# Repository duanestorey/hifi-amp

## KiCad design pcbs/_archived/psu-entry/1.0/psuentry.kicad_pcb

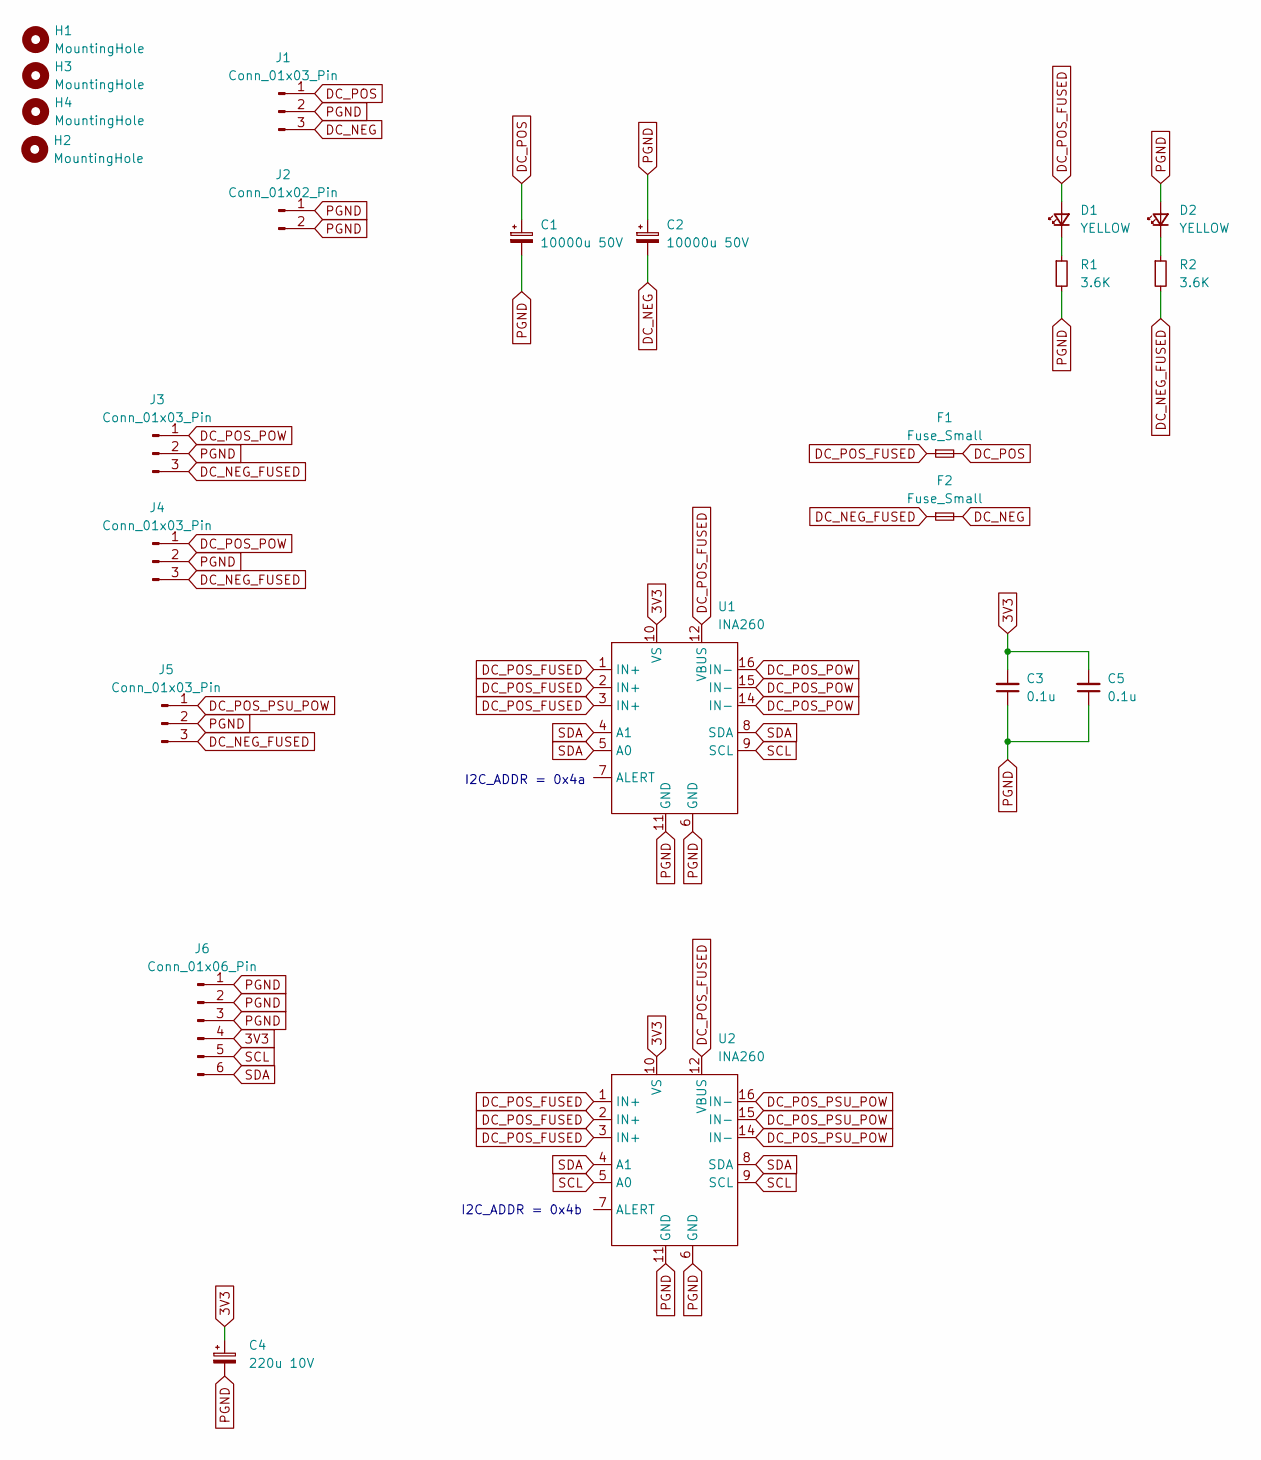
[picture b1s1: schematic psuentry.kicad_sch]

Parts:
C1, C2: 10000u 50V; CP_Radial_D25.0mm_P10.00mm_SnapIn
C3, C5: 0.1u; C_0805_2012Metric_Pad1.18x1.45mm_HandSolder
C4: 220u 10V; CP_Radial_D6.3mm_P2.50mm
D1, D2: YELLOW; LED_0805_2012Metric_Pad1.15x1.40mm_HandSolder
F1, F2: Fuse_Small; Aliexpress Fuse 5x20
H1, H2, H3, H4: MountingHole; MountingHole_3.2mm_M3_DIN965_Pad_TopOnly
J1, J3, J4, J5: Conn_01x03_Pin; JST_VH_B3P-VH-B_1x03_P3.96mm_Vertical
J2: Conn_01x02_Pin; JST_VH_B2P-VH-B_1x02_P3.96mm_Vertical
J6: Conn_01x06_Pin; JST_PH_B6B-PH-K_1x06_P2.00mm_Vertical
R1, R2: 3.6K; R_0603_1608Metric_Pad0.98x0.95mm_HandSolder
U1, U2: INA260; TSSOP-16_4.4x5mm_P0.65mm

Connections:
3V3: C3.2, C4.1, C5.2, J6.4, U1.10 (VS), U2.10 (VS)
DC_NEG: C2.2, F2.2, J1.3
DC_NEG_FUSED: F2.1, J3.3, J4.3, J5.3, R2.2
DC_POS: C1.1, F1.2, J1.1
DC_POS_FUSED: D1.2 (A), F1.1, U1.1 (IN+), U1.2 (IN+), U1.3 (IN+), U1.12 (VBUS), U2.1 (IN+), U2.2 (IN+), U2.3 (IN+), U2.12 (VBUS)
DC_POS_POW: J3.1, J4.1, U1.14 (IN-), U1.15 (IN-), U1.16 (IN-)
DC_POS_PSU_POW: J5.1, U2.14 (IN-), U2.15 (IN-), U2.16 (IN-)
unnamed: D1.1 (K), R1.1
unnamed: D2.1 (K), R2.1
PGND: C1.2, C2.1, C3.1, C4.2, C5.1, D2.2 (A), J1.2, J2.1, J2.2, J3.2, J4.2, J5.2, J6.1, J6.2, J6.3, R1.2, U1.6 (GND), U1.11 (GND), U2.6 (GND), U2.11 (GND)
SCL: J6.5, U1.9 (SCL), U2.5 (A0), U2.9 (SCL)
SDA: J6.6, U1.4 (A1), U1.5 (A0), U1.8 (SDA), U2.4 (A1), U2.8 (SDA)

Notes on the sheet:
I2C_ADDR = 0x4a
I2C_ADDR = 0x4b

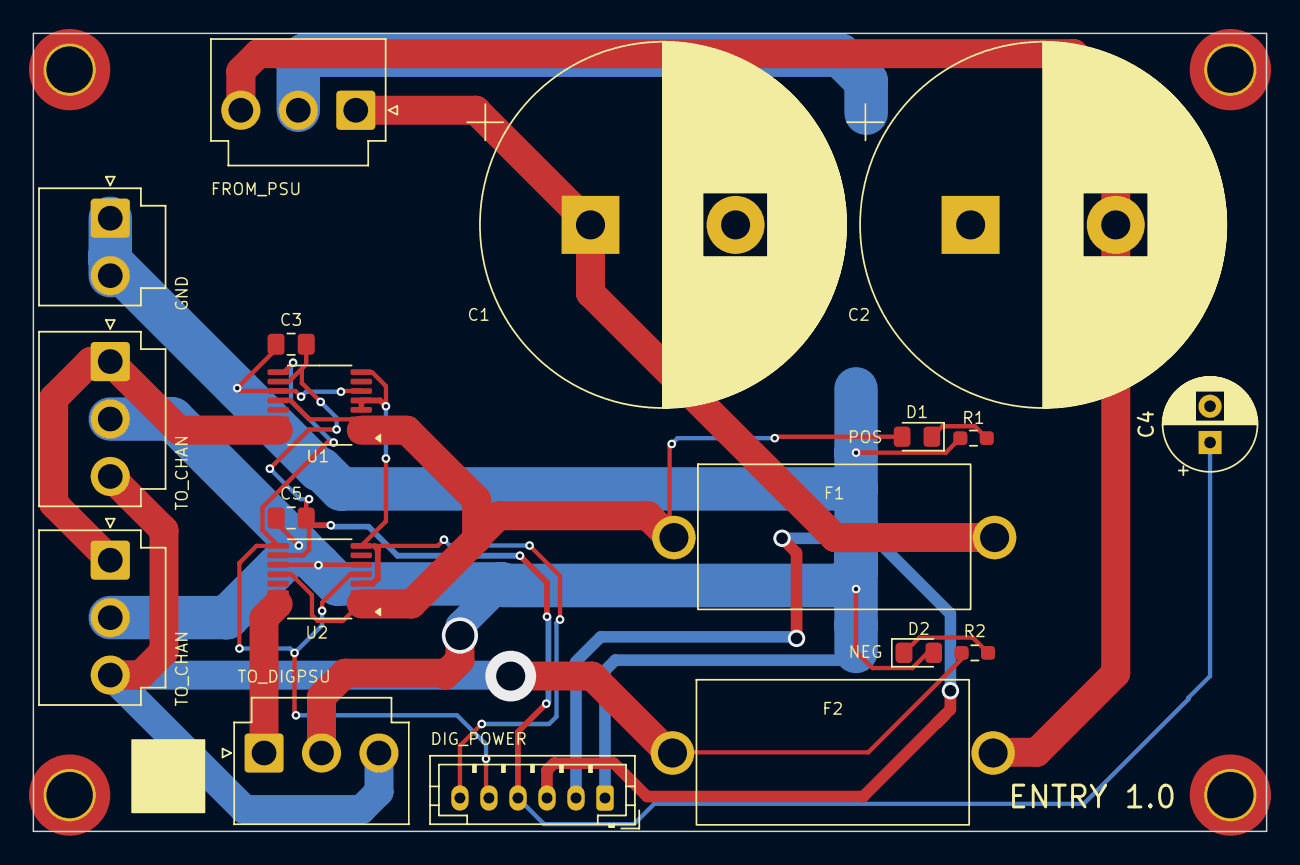
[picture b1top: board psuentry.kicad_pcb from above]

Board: 2 copper layers, 85.0 x 55.0 mm, 23 parts (0 on the bottom side), 12 nets.

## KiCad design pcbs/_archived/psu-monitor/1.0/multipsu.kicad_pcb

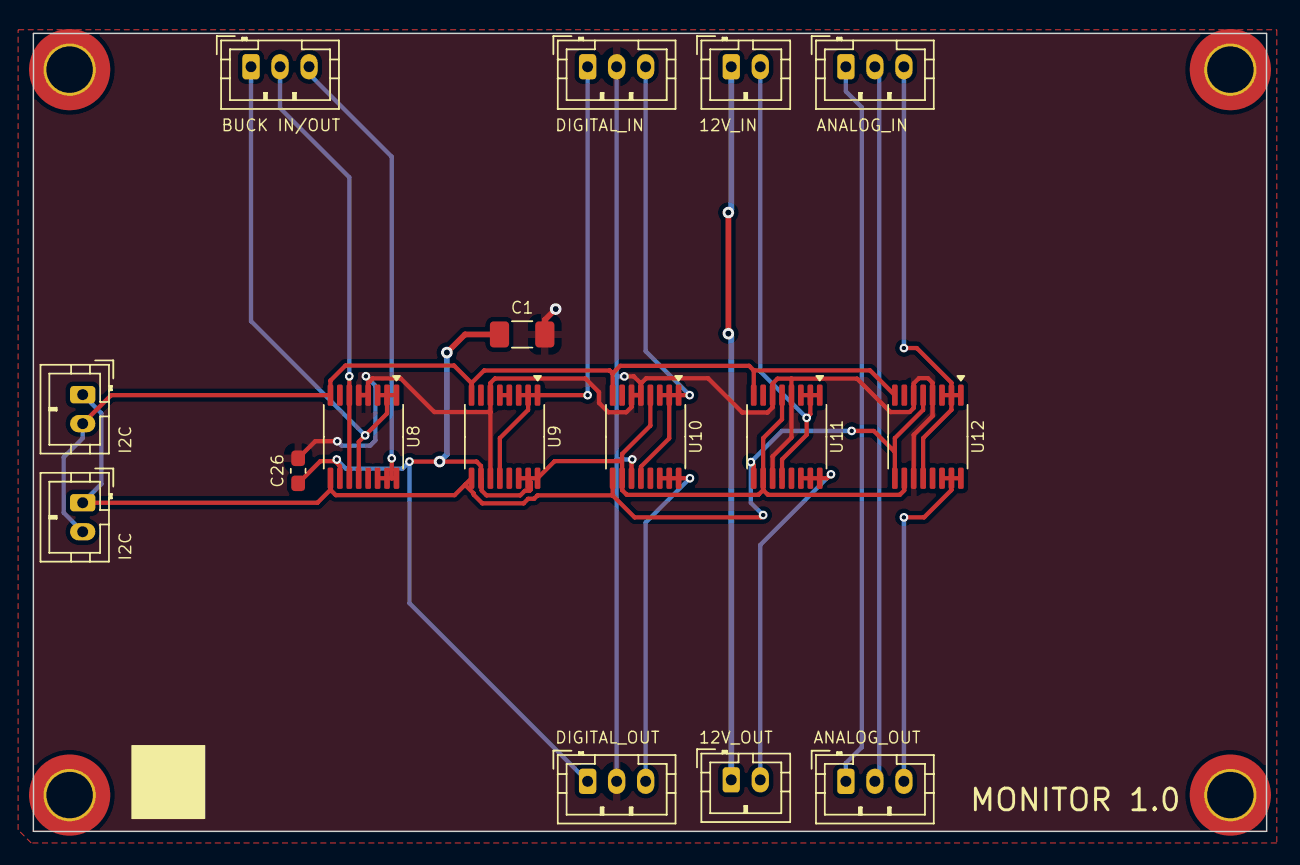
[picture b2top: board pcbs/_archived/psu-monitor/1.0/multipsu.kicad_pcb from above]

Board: 2 copper layers, 85.0 x 55.0 mm, 20 parts (0 on the bottom side), 18 nets.

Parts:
C1: 10u; C_1206_3216Metric_Pad1.33x1.80mm_HandSolder
C26: 0.1U; C_0603_1608Metric_Pad1.08x0.95mm_HandSolder
H1, H2, H3, H4: MountingHole; MountingHole_3.2mm_M3_DIN965_Pad_TopOnly
J1, J2, J5, J6, J7: Conn_01x03_Pin; JST_PH_B3B-PH-K_1x03_P2.00mm_Vertical
J3, J4, J8, J9: Conn_01x02_Pin; JST_PH_B2B-PH-K_1x02_P2.00mm_Vertical
U8, U9, U10, U11, U12: INA260; TSSOP-16_4.4x5mm_P0.65mm

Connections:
3V3: U9.4 (A1), U9.5 (A0)
3V3_IN: J2.1, U9.1 (IN+), U9.2 (IN+), U9.3 (IN+), U9.12 (VBUS)
3V3_OUT: C1.1, C26.1, J5.1, U8.10 (VS), U9.10 (VS), U9.14 (IN-), U9.15 (IN-), U9.16 (IN-), U10.4 (A1), U10.10 (VS), U11.5 (A0), U11.10 (VS), U12.10 (VS)
5V_IN: J2.3, U10.1 (IN+), U10.2 (IN+), U10.3 (IN+), U10.12 (VBUS)
5V_OUT: J5.3, U10.14 (IN-), U10.15 (IN-), U10.16 (IN-)
7V_IN: J1.1, U8.1 (IN+), U8.2 (IN+), U8.3 (IN+), U8.12 (VBUS)
7V_OUT: J1.3, U8.14 (IN-), U8.15 (IN-), U8.16 (IN-)
12V_IN: J8.2, U11.1 (IN+), U11.2 (IN+), U11.3 (IN+), U11.12 (VBUS)
12V_OUT: J4.2, U11.14 (IN-), U11.15 (IN-), U11.16 (IN-)
AGND: J6.2, J7.2
DC_NEG_OUT: J6.1, J7.1
DC_POS_IN: J7.3, U12.1 (IN+), U12.2 (IN+), U12.3 (IN+), U12.12 (VBUS)
DC_POS_OUT: J6.3, U12.14 (IN-), U12.15 (IN-), U12.16 (IN-)
GND: C1.2, C26.2, J2.2, J5.2, U8.4 (A1), U8.5 (A0), U9.6 (GND), U9.11 (GND), U10.5 (A0), U10.6 (GND), U10.11 (GND), U11.4 (A1), U11.6 (GND), U11.11 (GND), U12.4 (A1), U12.6 (GND), U12.11 (GND)
PGND: J1.2, U8.6 (GND), U8.11 (GND)
RELAY_GND: J4.1, J8.1
SCL: J3.1, J9.1, U8.9 (SCL), U9.9 (SCL), U10.9 (SCL), U11.9 (SCL), U12.5 (A0), U12.9 (SCL)
SDA: J3.2, J9.2, U8.8 (SDA), U9.8 (SDA), U10.8 (SDA), U11.8 (SDA), U12.8 (SDA)

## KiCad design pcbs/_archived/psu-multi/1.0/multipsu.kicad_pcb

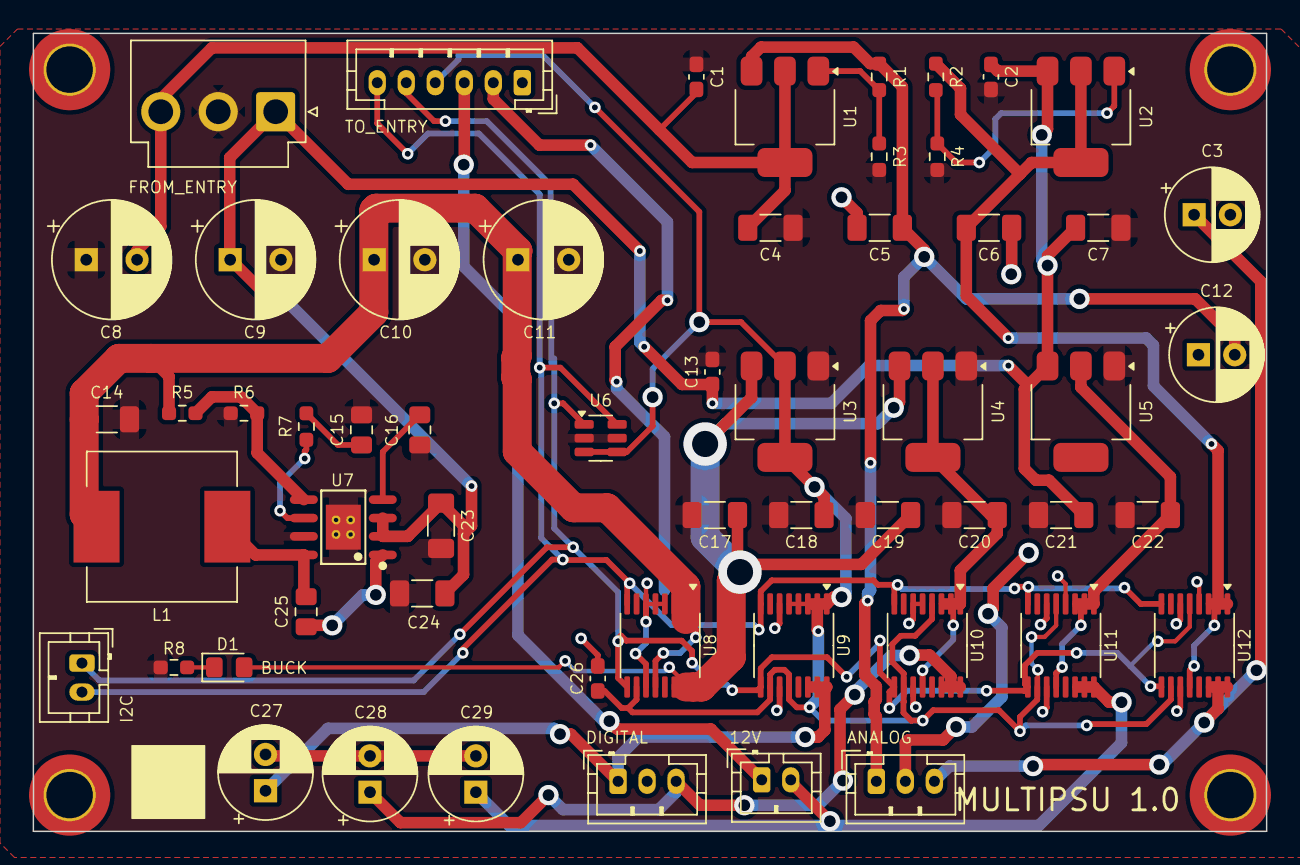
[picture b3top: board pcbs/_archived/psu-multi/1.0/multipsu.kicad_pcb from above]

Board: 2 copper layers, 85.0 x 55.0 mm, 61 parts (0 on the bottom side), 28 nets.

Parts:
C1, C2, C13, C26: 0.1U; C_0603_1608Metric_Pad1.08x0.95mm_HandSolder
C3, C12, C27, C28, C29: 470u 16V; CP_Radial_D6.3mm_P2.50mm
C4, C7, C21: 10u; C_1206_3216Metric_Pad1.33x1.80mm_HandSolder
C5, C6: 47U; C_1206_3216Metric_Pad1.33x1.80mm_HandSolder
C8, C9: 100u 50V; CP_Radial_D8.0mm_P3.50mm
C10, C11: 10V 470u; CP_Radial_D8.0mm_P3.50mm
C14, C23, C24: 10U 50V; C_1206_3216Metric_Pad1.33x1.80mm_HandSolder
C15: 0.22u; C_0805_2012Metric_Pad1.18x1.45mm_HandSolder
C16: 10n; C_0805_2012Metric_Pad1.18x1.45mm_HandSolder
C17, C18, C19, C20, C22: 10U; C_1206_3216Metric_Pad1.33x1.80mm_HandSolder
C25: 0.1u; C_0805_2012Metric_Pad1.18x1.45mm_HandSolder
D1: BLUE; LED_0805_2012Metric_Pad1.15x1.40mm_HandSolder
H1, H2, H3, H4: MountingHole; MountingHole_3.2mm_M3_DIN965_Pad_TopOnly
J1: Conn_01x06_Pin; JST_PH_B6B-PH-K_1x06_P2.00mm_Vertical
J2: Conn_01x03_Male; JST_VH_B3P-VH_1x03_P3.96mm_Vertical
J3, J4: Conn_01x02_Pin; JST_PH_B2B-PH-K_1x02_P2.00mm_Vertical
J5, J6: Conn_01x03_Pin; JST_PH_B3B-PH-K_1x03_P2.00mm_Vertical
L1: 10uH 21mOhm 5A; L_Vishay_IHLP-4040
R1, R2: 120R; R_0603_1608Metric_Pad0.98x0.95mm_HandSolder
R3, R4: 1.2K; R_0603_1608Metric_Pad0.98x0.95mm_HandSolder
R5: 160K; R_0603_1608Metric_Pad0.98x0.95mm_HandSolder
R6: 22.1K; R_0603_1608Metric_Pad0.98x0.95mm_HandSolder
R7: 86.6k; R_0603_1608Metric_Pad0.98x0.95mm_HandSolder
R8: 1.7K; R_0603_1608Metric_Pad0.98x0.95mm_HandSolder
U1: LM337_SOT223; SOT-223-3_TabPin2
U2: LM317_SOT-223; SOT-223-3_TabPin2
U3: ZLDO1117QG33TA; SOT-223-3_TabPin2
U4: AMS1117-5.0; SOT-223-3_TabPin2
U5: NCP1117-12; SOT-223
U6: TMP100; SOT-23-6
U7: AP64351SP-13; SOIC-8_L4.9-W3.9-P1.27-LS6.0-BL-EP
U8, U9, U10, U11, U12: INA260; TSSOP-16_4.4x5mm_P0.65mm

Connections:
3V3: C18.1, C26.1, J1.4, U3.2 (VO), U6.3 (ADD1), U6.4 (V+), U8.10 (VS), U9.1 (IN+), U9.2 (IN+), U9.3 (IN+), U9.4 (A1), U9.5 (A0), U9.10 (VS), U9.12 (VBUS), U10.4 (A1), U10.10 (VS), U11.5 (A0), U11.10 (VS), U12.10 (VS)
3V3_OUT: C27.1, J5.1, U9.14 (IN-), U9.15 (IN-), U9.16 (IN-)
5V: C20.1, U4.2 (VO), U10.1 (IN+), U10.2 (IN+), U10.3 (IN+), U10.12 (VBUS)
5V_OUT: C28.1, J5.3, U10.14 (IN-), U10.15 (IN-), U10.16 (IN-)
7V: C10.1, C11.1, C14.1, L1.2, R5.1, U8.1 (IN+), U8.2 (IN+), U8.3 (IN+), U8.12 (VBUS)
7V_OUT: C17.1, C19.1, D1.2 (A), U3.3 (VI), U4.3 (VI), U8.14 (IN-), U8.15 (IN-), U8.16 (IN-)
12V: C22.1, U5.2 (VO), U11.1 (IN+), U11.2 (IN+), U11.3 (IN+), U11.12 (VBUS)
12V_OUT: C29.1, J4.2, U11.14 (IN-), U11.15 (IN-), U11.16 (IN-)
AGND: C3.2, C5.1, C6.2, C12.1, J1.1, J6.2
DC_NEG_OUT: C5.2, C12.2, J6.1, R1.1, U1.3 (VO)
DC_POS: C6.1, R2.1, U2.2 (VO), U12.1 (IN+), U12.2 (IN+), U12.3 (IN+), U12.12 (VBUS)
DC_POS_OUT: C3.1, J6.3, U12.14 (IN-), U12.15 (IN-), U12.16 (IN-)
GND: C26.2, C27.2, C28.2, C29.2, J1.2, J5.2, U8.4 (A1), U8.5 (A0), U8.6 (GND), U8.11 (GND), U9.6 (GND), U9.11 (GND), U10.5 (A0), U10.6 (GND), U10.11 (GND), U11.4 (A1), U11.6 (GND), U11.11 (GND), U12.4 (A1), U12.6 (GND), U12.11 (GND)
unnamed: C15.1, R7.2
unnamed: D1.1 (K), R8.1
unnamed: R1.2, R3.1, U1.1 (ADJ)
unnamed: R2.2, R4.1, U2.1 (ADJ)
unnamed: C25.1, U7.1 (BST)
unnamed: R7.1, U7.6 (COMP)
unnamed: R5.2, R6.1, U7.5 (FB)
unnamed: C16.1, U7.4 (SS)
unnamed: C25.2, L1.1, U7.8 (SW)
PGND: C1.1, C2.2, C4.1, C7.2, C8.1, C9.2, C10.2, C11.2, C13.2, C14.2, C15.2, C16.2, C17.2, C18.2, C19.2, C20.2, C21.2, C22.2, C23.2, C24.2, J2.2, R3.2, R4.2, R6.2, R8.2, U3.1 (GND), U4.1 (GND), U5.1 (GND), U6.2 (GND), U6.5 (ADD0), U7.7 (GND), U7.9 (EP)
RELAY_GND: J1.3, J4.1
SCL: J1.5, J3.1, U6.1 (SCL), U8.9 (SCL), U9.9 (SCL), U10.9 (SCL), U11.9 (SCL), U12.5 (A0), U12.9 (SCL)
SDA: J1.6, J3.2, U6.6 (SDA), U8.8 (SDA), U9.8 (SDA), U10.8 (SDA), U11.8 (SDA), U12.8 (SDA)
VN: C1.2, C4.2, C8.2, J2.3, U1.2 (VI)
VP: C2.1, C7.1, C9.1, C13.1, C21.1, C23.1, C24.1, J2.1, U2.3 (VI), U5.3 (VI), U7.2 (VIN), U7.3 (EN)

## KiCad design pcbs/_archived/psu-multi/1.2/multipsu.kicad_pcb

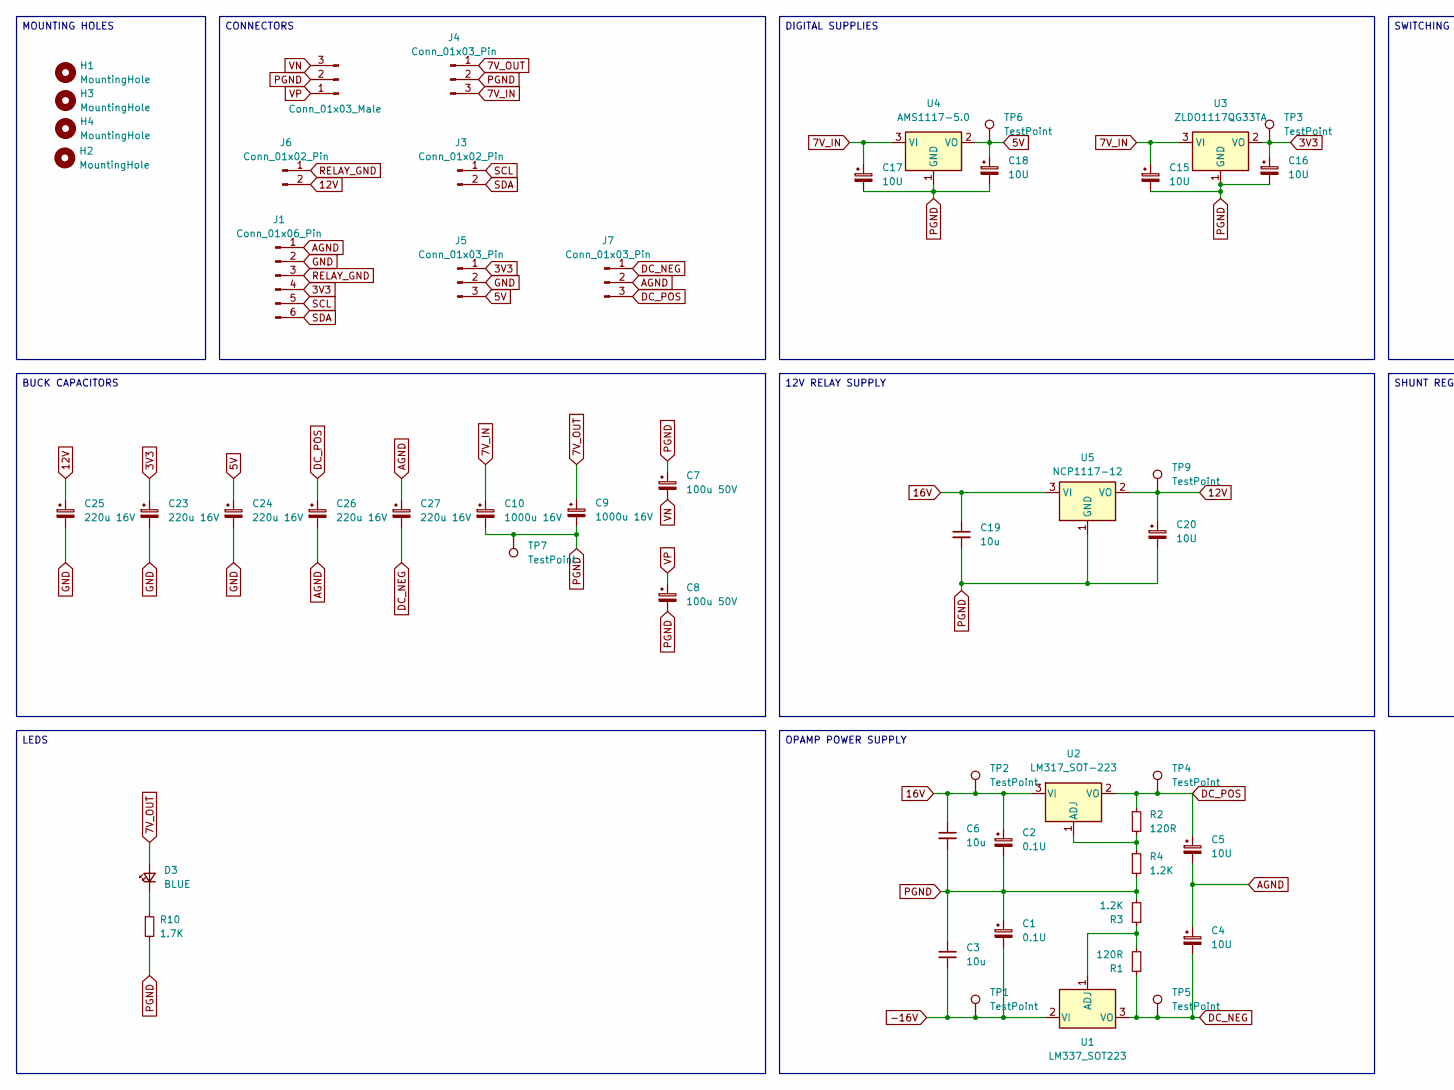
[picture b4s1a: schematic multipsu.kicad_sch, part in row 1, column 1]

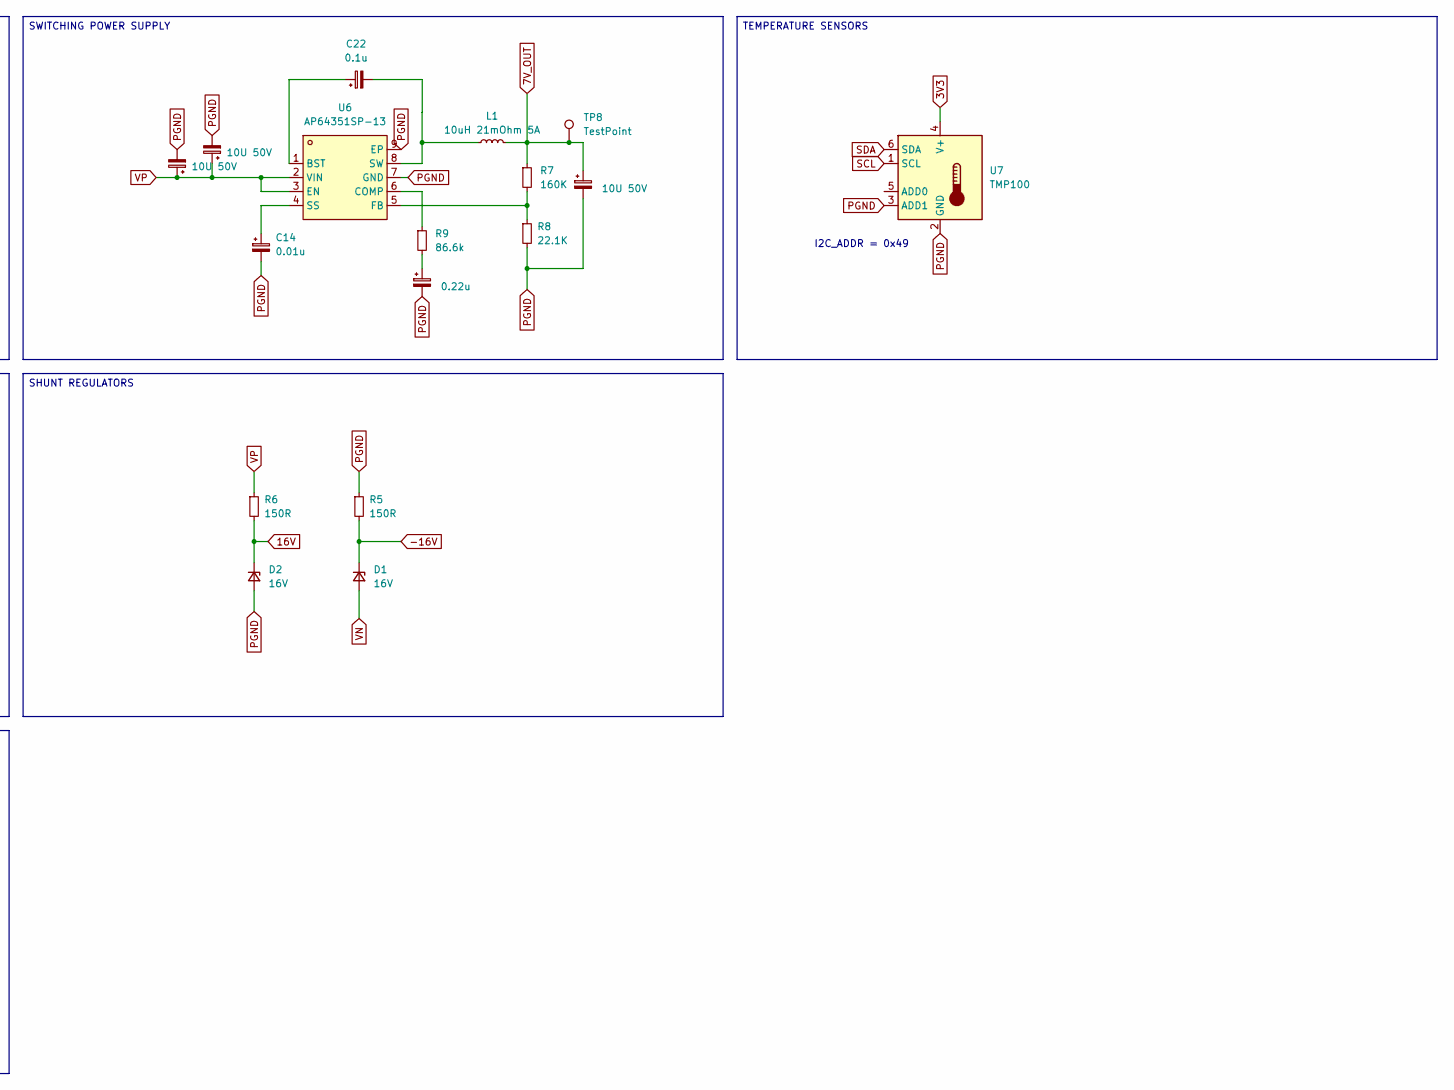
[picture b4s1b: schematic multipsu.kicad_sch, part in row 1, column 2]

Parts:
C1, C2: 0.1U; C_0805_2012Metric_Pad1.18x1.45mm_HandSolder
C3, C6, C19: 10u; C_1206_3216Metric_Pad1.33x1.80mm_HandSolder
C4, C5, C15, C16, C17, C18, C20: 10U; C_1206_3216Metric_Pad1.33x1.80mm_HandSolder
C7, C8: 100u 50V; CP_Radial_D8.0mm_P3.50mm; Mouser RGA101M1HBK-0811G
C9, C10: 1000u 16V; CP_Radial_D8.0mm_P3.50mm
C11, C12, C21: 10U 50V; C_1206_3216Metric_Pad1.33x1.80mm_HandSolder
C13: 0.22u; C_0805_2012Metric_Pad1.18x1.45mm_HandSolder
C14: 0.01u; C_0805_2012Metric_Pad1.18x1.45mm_HandSolder
C22: 0.1u; C_0805_2012Metric_Pad1.18x1.45mm_HandSolder
C23, C24, C25, C26, C27: 220u 16V; CP_Radial_D6.3mm_P2.50mm
D1, D2: 16V; D_SMA; Mouser 833-SMA2Z16AQ-TP
D3: BLUE; LED_0805_2012Metric_Pad1.15x1.40mm_HandSolder
H1, H2, H3, H4: MountingHole; MountingHole_3.2mm_M3_DIN965_Pad_TopOnly
J1: Conn_01x06_Pin; JST_PH_B6B-PH-K_1x06_P2.00mm_Vertical
J2: Conn_01x03_Male; JST_VH_B3P-VH_1x03_P3.96mm_Vertical
J3, J6: Conn_01x02_Pin; JST_PH_B2B-PH-K_1x02_P2.00mm_Vertical
J4, J5, J7: Conn_01x03_Pin; JST_PH_B3B-PH-K_1x03_P2.00mm_Vertical
L1: 10uH 21mOhm 5A; L_Vishay_IHLP-4040; Mouser 704-DR1040-7R0-R
R1, R2: 120R; R_0603_1608Metric_Pad0.98x0.95mm_HandSolder
R3, R4: 1.2K; R_0603_1608Metric_Pad0.98x0.95mm_HandSolder
R5, R6: 150R; R_2512_6332Metric_Pad1.40x3.35mm_HandSolder; Mouser 279-CRGH2512J150R
R7: 160K; R_0603_1608Metric_Pad0.98x0.95mm_HandSolder; Mouser 603-RC0603JR-10180KL
R8: 22.1K; R_0603_1608Metric_Pad0.98x0.95mm_HandSolder; Mouser 603-RC0603JR-07820KP
R9: 86.6k; R_0603_1608Metric_Pad0.98x0.95mm_HandSolder; Mouser 71-CRCW0603-86.6K-E3
R10: 1.7K; R_0603_1608Metric_Pad0.98x0.95mm_HandSolder; Mouser 603-RC0603JR-07820KP
TP1, TP2, TP3, TP4, TP5, TP6, TP7, TP8, TP9: TestPoint; TestPoint_THTPad_D2.0mm_Drill1.0mm
U1: LM337_SOT223; SOT-223-3_TabPin2; Mouser 926-LM337IMPX/NOPB
U2: LM317_SOT-223; SOT-223-3_TabPin2; Mouser 595-LM317DCY
U3: ZLDO1117QG33TA; SOT-223-3_TabPin2; Mouser ZLDO1117QG33TA
U4: AMS1117-5.0; SOT-223-3_TabPin2; Mouser 926-LM1117MPX5.0NOPB
U5: NCP1117-12; SOT-223; Mouser 863-NCP1117ST12T3G
U6: AP64351SP-13; SOIC-8_L4.9-W3.9-P1.27-LS6.0-BL-EP; LCSC Part C3192339
U7: TMP100; SOT-23-6

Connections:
3V3: C16.1, C23.1, J1.4, J5.1, TP3.1, U3.2 (VO), U7.4 (V+)
5V: C18.1, C24.1, J5.3, TP6.1, U4.2 (VO)
7V_IN: C10.1, C15.1, C17.1, J4.3, U3.3 (VI), U4.3 (VI)
7V_OUT: C9.1, C11.1, D3.2 (A), J4.1, L1.2, R7.1, TP8.1
12V: C20.1, C25.1, J6.2, TP9.1, U5.2 (VO)
16V: C2.1, C6.1, C19.1, D2.1 (K), R6.2, TP2.1, U2.3 (VI), U5.3 (VI)
-16V: C1.2, C3.2, D1.1 (K), R5.2, TP1.1, U1.2 (VI)
AGND: C4.1, C5.2, C26.2, C27.1, J1.1, J7.2
DC_NEG: C4.2, C27.2, J7.1, R1.1, TP5.1, U1.3 (VO)
DC_POS: C5.1, C26.1, J7.3, R2.1, TP4.1, U2.2 (VO)
GND: C23.2, C24.2, C25.2, J1.2, J5.2
unnamed: C13.1, R9.2
unnamed: D3.1 (K), R10.1
unnamed: R1.2, R3.1, U1.1 (ADJ)
unnamed: R2.2, R4.1, U2.1 (ADJ)
unnamed: C22.1, U6.1 (BST)
unnamed: R9.1, U6.6 (COMP)
unnamed: R7.2, R8.1, U6.5 (FB)
unnamed: C14.1, U6.4 (SS)
unnamed: C22.2, L1.1, U6.8 (SW)
PGND: C1.1, C2.2, C3.1, C6.2, C7.1, C8.2, C9.2, C10.2, C11.2, C12.2, C13.2, C14.2, C15.2, C16.2, C17.2, C18.2, C19.2, C20.2, C21.2, D2.2 (A), J2.2, J4.2, R3.2, R4.2, R5.1, R8.2, R10.2, TP7.1, U3.1 (GND), U4.1 (GND), U5.1 (GND), U6.7 (GND), U6.9 (EP), U7.2 (GND), U7.3 (ADD1)
RELAY_GND: J1.3, J6.1
SCL: J1.5, J3.1, U7.1 (SCL)
SDA: J1.6, J3.2, U7.6 (SDA)
VN: C7.2, D1.2 (A), J2.3
VP: C8.1, C12.1, C21.1, J2.1, R6.1, U6.2 (VIN), U6.3 (EN)

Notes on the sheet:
I2C_ADDR = 0x49
CONNECTORS
DIGITAL SUPPLIES
SHUNT REGULATORS
TEMPERATURE SENSORS
BUCK CAPACITORS
MOUNTING HOLES
OPAMP POWER SUPPLY
12V RELAY SUPPLY
SWITCHING POWER SUPPLY
LEDS

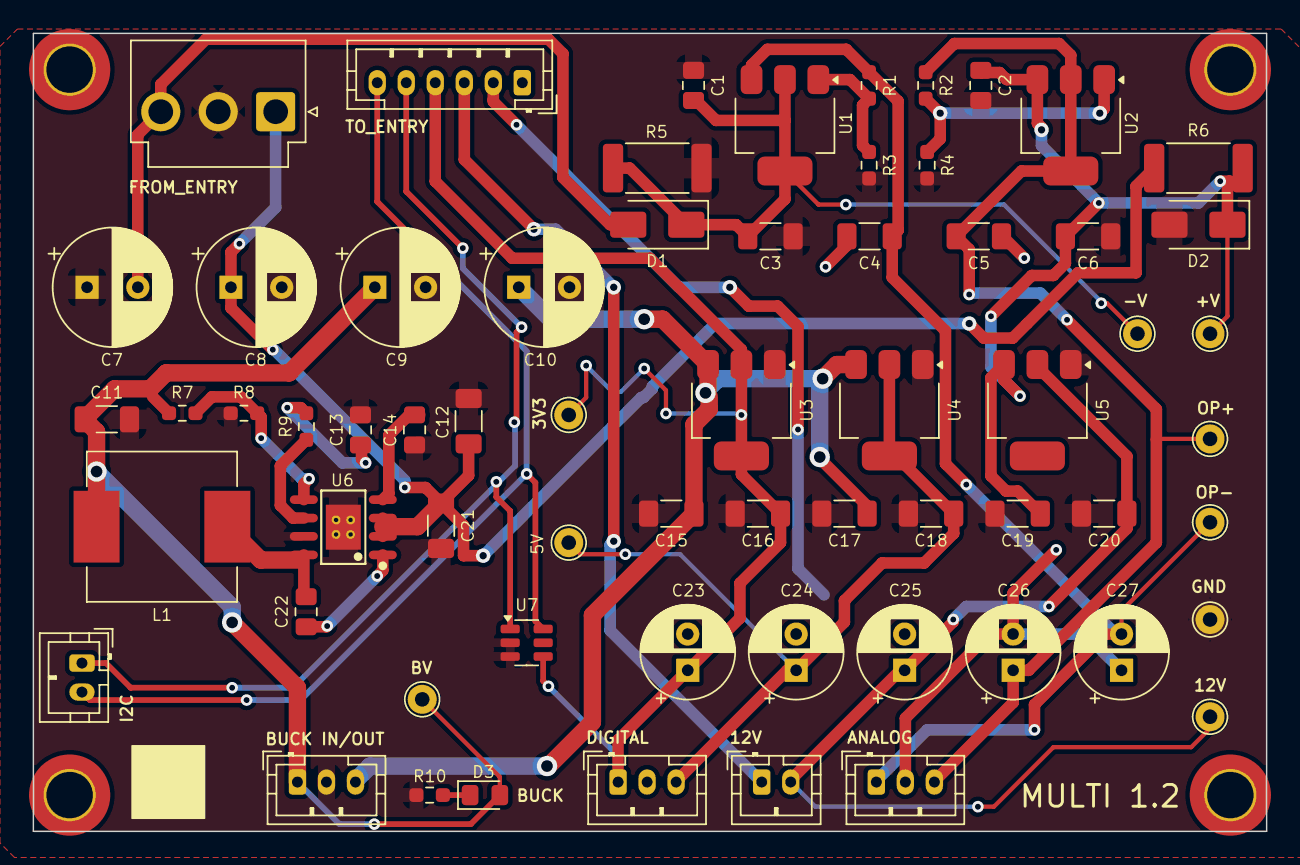
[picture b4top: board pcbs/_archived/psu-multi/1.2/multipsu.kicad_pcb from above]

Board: 2 copper layers, 85.0 x 55.0 mm, 68 parts (0 on the bottom side), 26 nets.

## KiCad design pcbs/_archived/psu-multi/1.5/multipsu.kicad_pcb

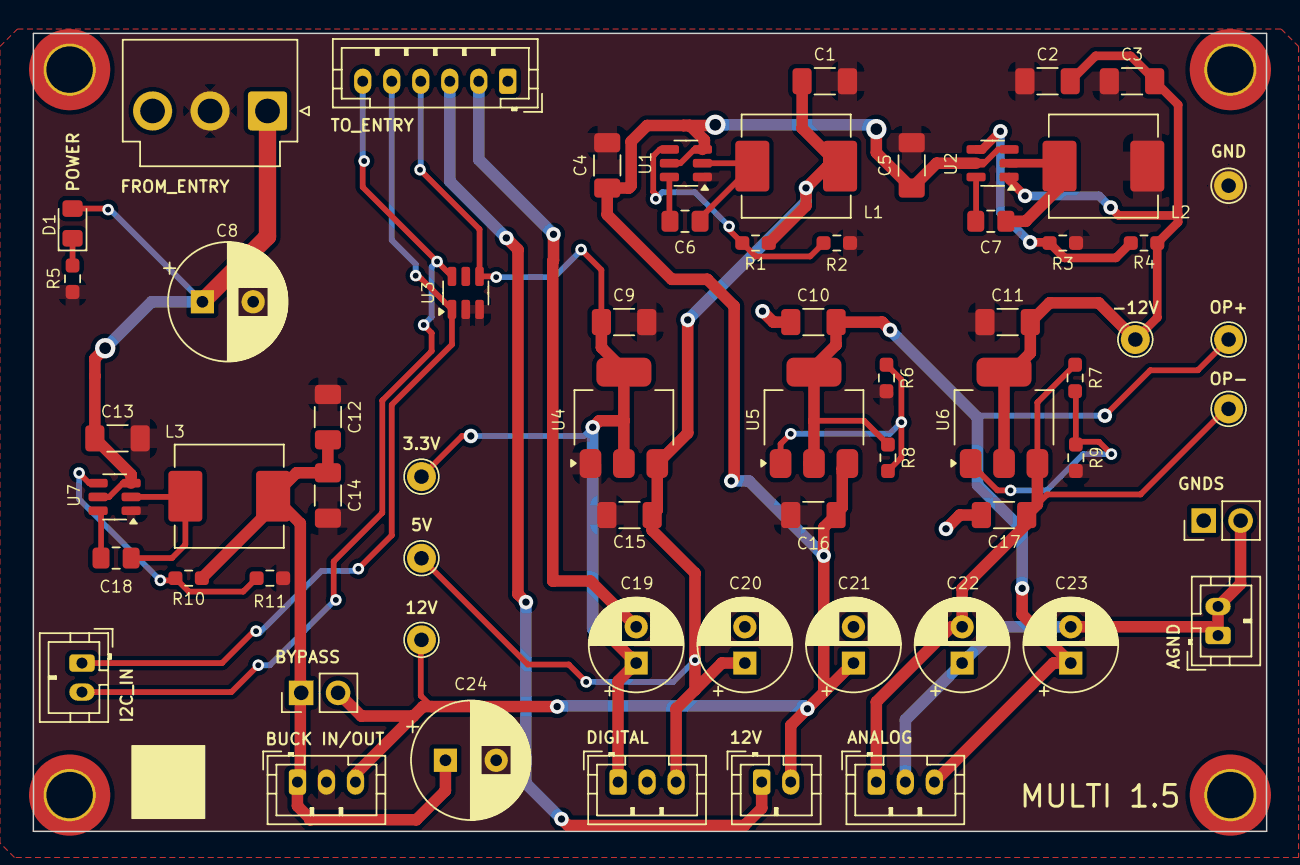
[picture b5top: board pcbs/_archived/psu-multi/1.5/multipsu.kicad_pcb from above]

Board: 2 copper layers, 85.0 x 55.0 mm, 67 parts (0 on the bottom side), 27 nets.

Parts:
C1, C2, C3, C12, C14: 22U 25V; C_1206_3216Metric_Pad1.33x1.80mm_HandSolder
C4, C5, C13: 10U 50V; C_1206_3216Metric_Pad1.33x1.80mm_HandSolder
C6, C7, C18: 0.1u; C_0805_2012Metric_Pad1.18x1.45mm_HandSolder
C8: 100u 50V; CP_Radial_D8.0mm_P3.50mm
C9, C10, C15, C17: 10U; C_1206_3216Metric_Pad1.33x1.80mm_HandSolder
C11, C16: 10u; C_1206_3216Metric_Pad1.33x1.80mm_HandSolder
C19, C20, C21, C22, C23: 220u 16V; CP_Radial_D6.3mm_P2.50mm
C24: 1000u 16V; CP_Radial_D8.0mm_P3.50mm
D1: BLUE; LED_0805_2012Metric_Pad1.15x1.40mm_HandSolder
H1, H2, H3, H4: MountingHole; MountingHole_3.2mm_M3_DIN965_Pad_TopOnly
J1: Conn_01x06_Pin; JST_PH_B6B-PH-K_1x06_P2.00mm_Vertical
J2: Conn_01x03_Male; JST_VH_B3P-VH_1x03_P3.96mm_Vertical
J3, J10: Conn_01x02; PinHeader_1x02_P2.54mm_Vertical
J4, J5, J8: Conn_01x02_Pin; JST_PH_B2B-PH-K_1x02_P2.00mm_Vertical
J6, J7, J9: Conn_01x03_Pin; JST_PH_B3B-PH-K_1x03_P2.00mm_Vertical
L1: 3.3u; L_Sunlord_MWSA0605S
L2, L3: 6.8u; L_Sunlord_MWSA0605S
R1, R3, R10: 100K; R_0603_1608Metric_Pad0.98x0.95mm_HandSolder
R2: 13.7K; R_0603_1608Metric_Pad0.98x0.95mm_HandSolder
R4, R11: 5.23K; R_0603_1608Metric_Pad0.98x0.95mm_HandSolder
R5: 16K; R_0603_1608Metric_Pad0.98x0.95mm_HandSolder
R6, R9: 1.6K; R_0603_1608Metric_Pad0.98x0.95mm_HandSolder
R7, R8: 240R; R_0603_1608Metric_Pad0.98x0.95mm_HandSolder
TP1, TP2, TP3, TP4, TP5, TP6, TP7: TestPoint; TestPoint_THTPad_D2.0mm_Drill1.0mm
U1, U2, U7: LMR51430; SOT-23-6
U3: TMP100; SOT-23-6
U4: ZLDO1117QG33TA; SOT-223-3_TabPin2
U5: LM317_SOT-223; SOT-223-3_TabPin2
U6: LM337_SOT223; SOT-223-3_TabPin2

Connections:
3V3: C9.1, C19.1, J1.4, J7.1, TP5.1, U3.4 (V+), U4.2 (VO)
5V: C1.1, C15.1, C20.1, J7.3, L1.2, R1.1, TP6.1, U4.3 (VI)
12V: C4.1, C5.1, C16.1, C21.1, J6.3, J8.2, J10.2, TP7.1, U1.3 (VIN), U1.5 (EN), U2.3 (VIN), U2.5 (EN), U5.3 (VI)
12V_OUT: C12.1, C14.1, C24.1, J6.1, J10.1, L3.2, R10.1
-12V: C2.2, C3.2, C11.2, R4.2, TP2.1, U2.1 (GND), U6.2 (VI)
AGND: C10.2, C17.1, J1.1, J3.1
AGND_INT: C22.1, C23.2, J3.2, J4.1, J4.2, J9.2
DC_NEG: C17.2, C22.2, J9.1, R7.1, TP4.1, U6.3 (VO)
DC_POS: C10.1, C23.1, J9.3, R8.1, TP3.1, U5.2 (VO)
GND: C19.2, C20.2, C21.2, J1.2, J7.2
unnamed: D1.1 (K), R5.1
unnamed: C6.1, U1.6 (CB)
unnamed: R1.2, R2.1, U1.4 (FB)
unnamed: C6.2, L1.1, U1.2 (SW)
unnamed: C7.1, U2.6 (CB)
unnamed: R3.2, R4.1, U2.4 (FB)
unnamed: C7.2, L2.1, U2.2 (SW)
unnamed: R6.1, R8.2, U5.1 (ADJ)
unnamed: R7.2, R9.1, U6.1 (ADJ)
unnamed: C18.1, U7.6 (CB)
unnamed: R10.2, R11.1, U7.4 (FB)
unnamed: C18.2, L3.1, U7.2 (SW)
PGND: C1.2, C2.1, C3.1, C4.2, C5.2, C8.2, C9.2, C11.1, C12.2, C13.2, C14.2, C15.2, C16.2, C24.2, J2.2, J6.2, L2.2, R2.2, R3.1, R5.2, R6.2, R9.2, R11.2, TP1.1, U1.1 (GND), U3.2 (GND), U3.3 (ADD1), U4.1 (GND), U7.1 (GND)
RELAY_GND: J1.3, J8.1
SCL: J1.5, J5.1, U3.1 (SCL)
SDA: J1.6, J5.2, U3.6 (SDA)
VP: C8.1, C13.1, D1.2 (A), J2.1, U7.3 (VIN), U7.5 (EN)
